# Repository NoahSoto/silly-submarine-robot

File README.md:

# Just a #silly-submarine !!!

To get a detailed recount of my design process to make this project come to fruition, please check out my Medium post!

Medium: https://medium.com/@noah.soto/my-first-robot-building-a-silly-submarine-a711a566f621

Please checkout the ESP32 branch for PCB designs, and my most updated code!

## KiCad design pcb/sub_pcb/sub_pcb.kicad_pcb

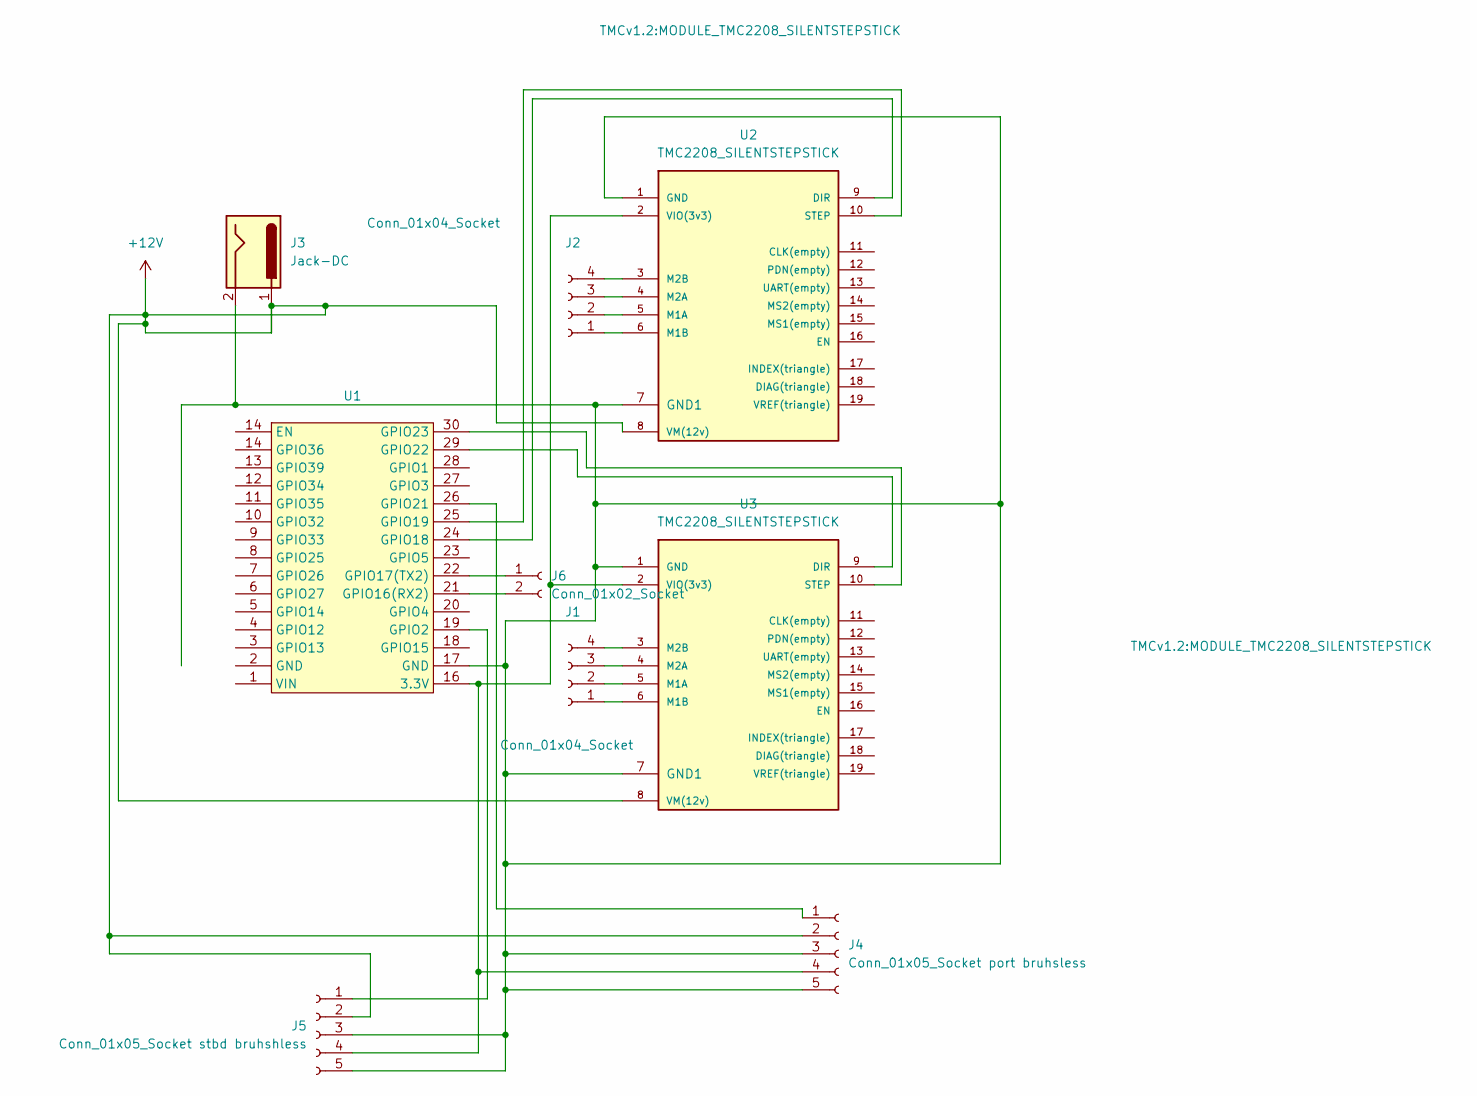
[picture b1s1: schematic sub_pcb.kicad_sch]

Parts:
J1, J2: Conn_01x04_Socket; PinHeader_1x04_P2.54mm_Horizontal
J3: Jack-DC; BarrelJack_CUI_PJ-102AH_Horizontal
J4: Conn_01x05_Socket port bruhsless; PinHeader_1x05_P2.54mm_Horizontal
J5: Conn_01x05_Socket stbd bruhshless; PinHeader_1x05_P2.54mm_Horizontal
J6: Conn_01x02_Socket; PinHeader_1x02_P2.54mm_Horizontal
U1: ESP32-DevKitV1-DOIT
U2, U3: TMC2208_SILENTSTEPSTICK; MODULE_TMC2208_SILENTSTEPSTICK

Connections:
+12V: J3.1, J4.2, J5.2, U2.8 (VM(12v)), U3.8 (VM(12v))
unnamed: J1.1, U3.6 (M1B)
unnamed: J1.2, U3.5 (M1A)
unnamed: J1.3, U3.4 (M2A)
unnamed: J1.4, U3.3 (M2B)
unnamed: J2.1, U2.6 (M1B)
unnamed: J2.2, U2.5 (M1A)
unnamed: J2.3, U2.4 (M2A)
unnamed: J2.4, U2.3 (M2B)
unnamed: J4.1, U1.26 (GPIO21)
unnamed: J3.2, J4.3, J4.5, J5.3, J5.5, U1.17 (GND), U2.1 (GND), U2.7 (GND1), U3.1 (GND), U3.7 (GND1)
unnamed: J4.4, J5.4, U1.16 (3.3V), U2.2 (VIO(3v3)), U3.2 (VIO(3v3))
unnamed: J5.1, U1.19 (GPIO2)
unnamed: J6.1, U1.22 (GPIO17(TX2))
unnamed: J6.2, U1.21 (GPIO16(RX2))
unnamed: U1.24 (GPIO18), U2.9 (DIR)
unnamed: U1.25 (GPIO19), U2.10 (STEP)
unnamed: U1.29 (GPIO22), U3.9 (DIR)
unnamed: U1.30 (GPIO23), U3.10 (STEP)

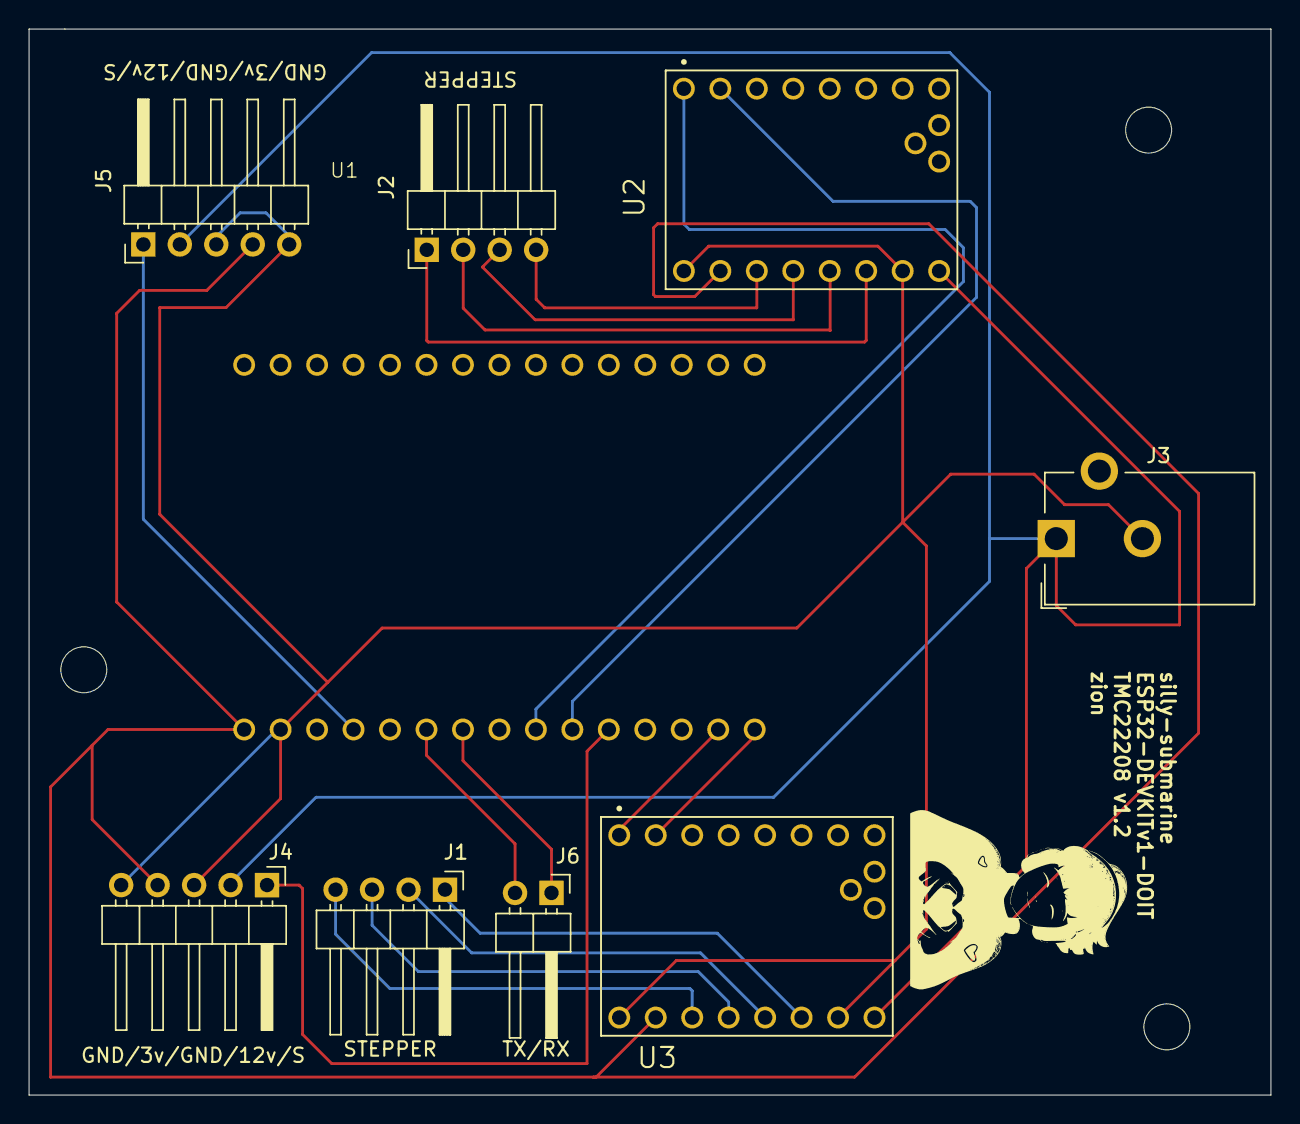
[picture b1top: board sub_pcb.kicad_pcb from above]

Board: 2 copper layers, 86.5 x 74.2 mm, 9 parts (0 on the bottom side), 19 nets.

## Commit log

2025-01-03 Blinky!
2025-01-03 stepper (it does technically move but not well)
2025-01-05 web server + stepper motors tmc2208's up and running!
2025-01-05 ESC variable thrust from POST input
2025-01-06 left and right thruster control
2025-01-15 ESP32 branch - controller code testing
2025-01-15 stepper works, brushless doesnt yet
2025-01-15 WORKING BRUHSLESS AND STEPPER CODE. The wiring was weird this go around...
2025-01-15 code that i want to test
2025-01-15 minor change
2025-01-18 nearly fully working code
2025-01-26 KICAD PCB Design & Gerber files
    Design and production files for the silly-submarine 2 layer PCB! Its my first PCB too, lots of fun awesome project especially w the JLC PCB sale
2025-02-21 fixing comms via pin 2
2025-03-09 medium article
    https://medium.com/@noah.soto/my-first-robot-building-a-silly-submarine-a711a566f621
